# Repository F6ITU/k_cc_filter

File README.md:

# k_cc_filter
Simple DC filter for Power Switching Unit (12 or 45V) (codename "Boufiltre")

The whole network as a 100V service voltage 

L1/L4 could be omited and replaced by jumpers.

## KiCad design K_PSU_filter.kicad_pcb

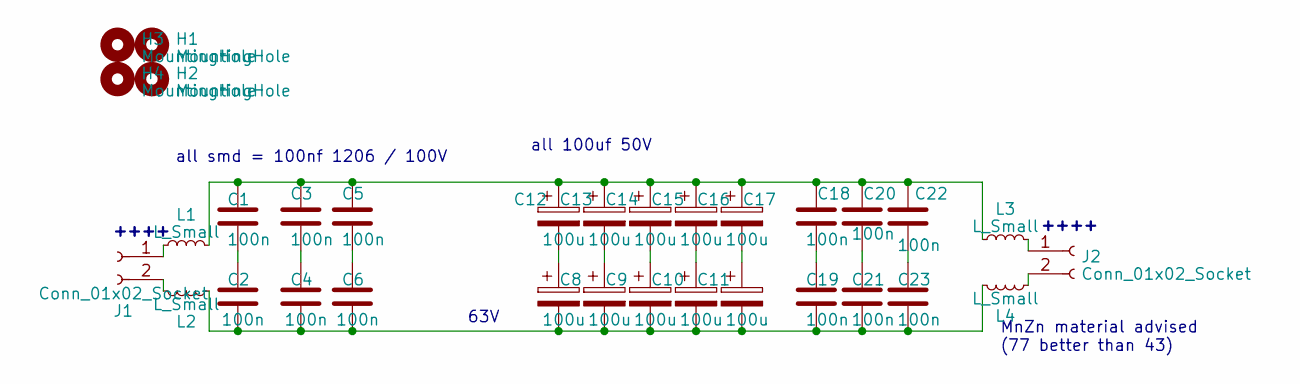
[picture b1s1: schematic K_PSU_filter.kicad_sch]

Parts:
C1, C2, C3, C4, C5, C6, C18, C19, C20, C21, C22, C23: 100n; C_1206_3216Metric_Pad1.33x1.80mm_HandSolder
C8, C9, C10, C11, C12, C13, C14, C15, C16, C17: 100u; CP_Radial_D10.0mm_P5.00mm
H1, H2, H3, H4: MountingHole; MountingHole_3.2mm_M3_Pad
J1, J2: Conn_01x02_Socket; 1711725
L1, L2, L3, L4: L_Small; L_Toroid_Horizontal_25x22

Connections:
unnamed: C1.1, C3.1, C5.1, C13.1, C14.1, C15.1, C16.1, C17.1, C18.1, C20.1, C22.1, L1.2, L3.1
unnamed: C1.2, C2.1
unnamed: C3.2, C4.1
unnamed: C5.2, C6.1
unnamed: C10.1, C15.2
unnamed: C2.2, C4.2, C6.2, C8.2, C9.2, C10.2, C11.2, C12.2, C19.2, C21.2, C23.2, L2.2, L4.1
unnamed: C11.1, C16.2
unnamed: C12.1, C17.2
unnamed: C8.1, C13.2
unnamed: C9.1, C14.2
unnamed: C18.2, C19.1
unnamed: C20.2, C21.1
unnamed: C22.2, C23.1
unnamed: J1.1, L1.1
unnamed: J1.2, L2.1
unnamed: J2.1, L3.2
unnamed: J2.2, L4.2

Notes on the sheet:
MnZn material advised (77 better than 43)
all smd = 100nf 1206 / 100V
63V
++++
all 100uf 50V

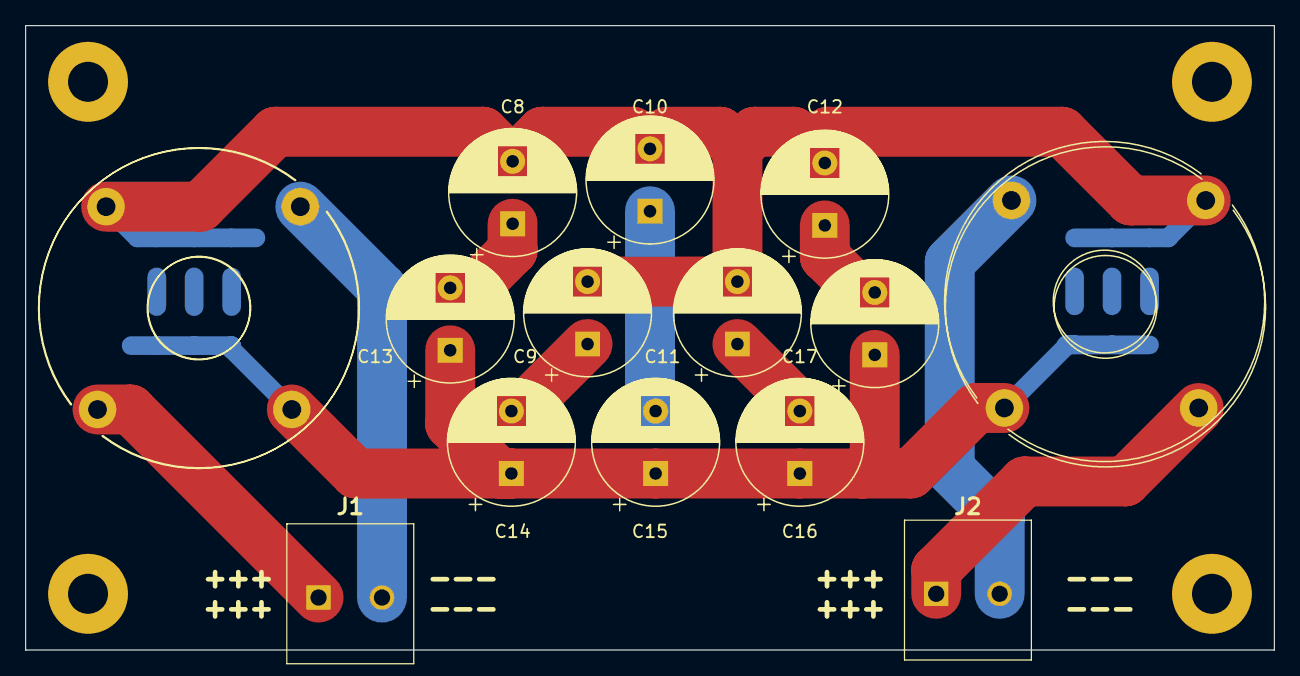
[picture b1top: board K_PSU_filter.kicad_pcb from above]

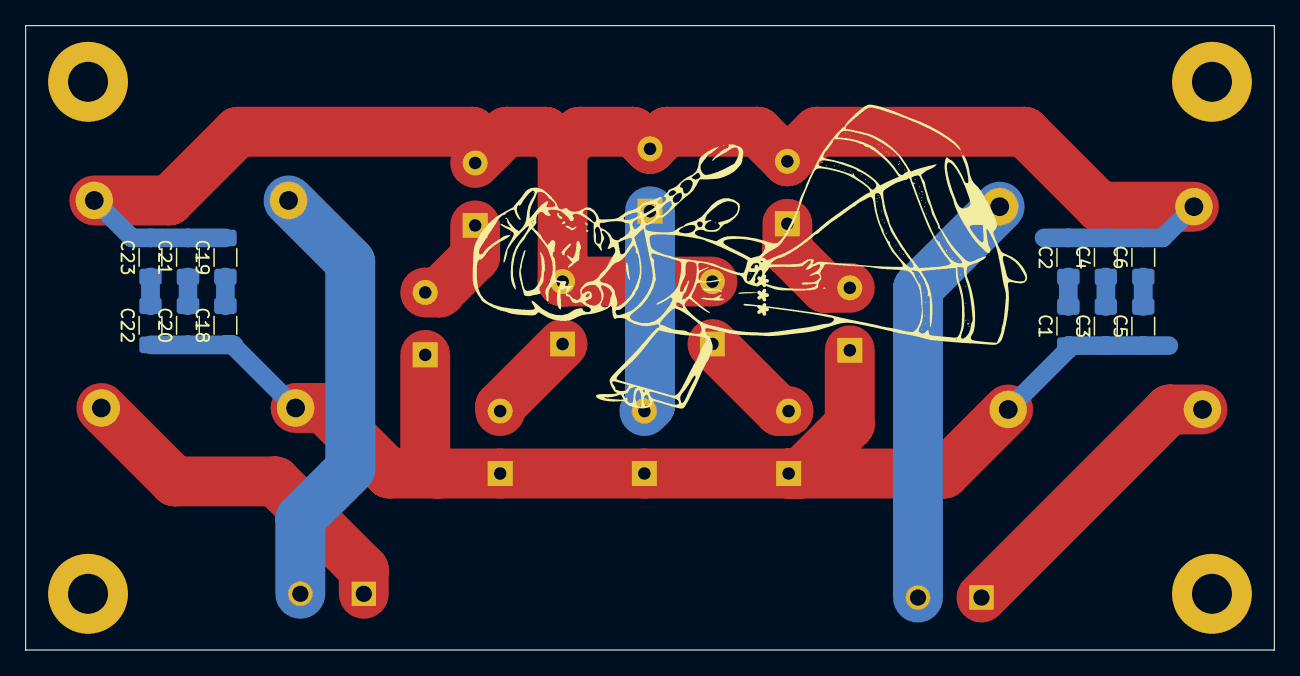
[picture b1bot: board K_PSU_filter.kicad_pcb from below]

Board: 2 copper layers, 100.0 x 50.0 mm, 32 parts (12 on the bottom side), 17 nets.

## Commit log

2023-06-27 schematic and routing completed
2023-06-27 gerber added, small silkmask mods
2023-06-28 new 3D capture, new gerber
2023-06-28 new readme
2023-07-21 small routing mods, new gerber, inductors are in the same direct.
